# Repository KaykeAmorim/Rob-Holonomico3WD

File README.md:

# Robô Holonômico 3WD

Robô desenvolvido no Colégio Técnico da UFMG (Coltec) com o intuito de auxiliar o ensino de Robótica aos estudantes.

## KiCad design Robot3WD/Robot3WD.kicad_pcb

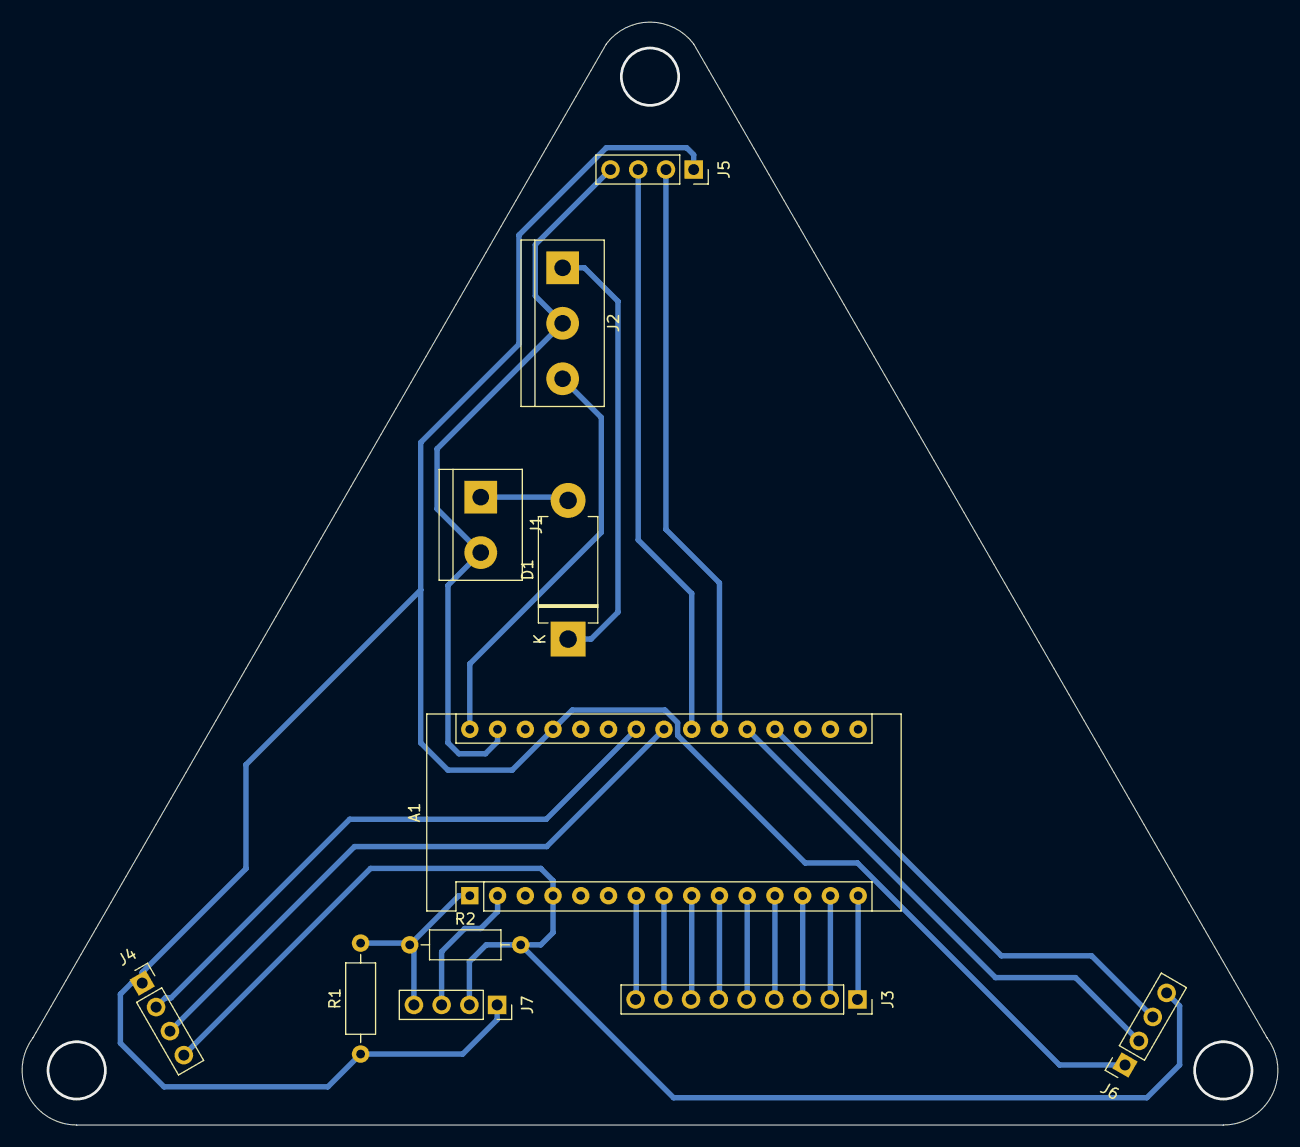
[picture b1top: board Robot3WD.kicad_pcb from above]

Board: 2 copper layers, 115.0 x 101.0 mm, 11 parts (0 on the bottom side), 22 nets.

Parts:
A1: Arduino_Nano_v2.x; Arduino_Nano
D1: 1N5404; D_DO-201AD_P12.70mm_Horizontal
J1: Battery; TerminalBlock_bornier-2_P5.08mm
J2: L298N; TerminalBlock_bornier-3_P5.08mm
J3: Motores; PinSocket_1x09_P2.54mm_Vertical
J4: HC-SR04a; PinSocket_1x04_P2.54mm_Vertical
J5: HC-SR04b; PinSocket_1x04_P2.54mm_Vertical
J6: HC-SR04c; PinSocket_1x04_P2.54mm_Vertical
J7: HC-06; PinSocket_1x04_P2.54mm_Vertical
R1: 1k; R_Axial_DIN0207_L6.3mm_D2.5mm_P10.16mm_Horizontal
R2: 2.2k; R_Axial_DIN0207_L6.3mm_D2.5mm_P10.16mm_Horizontal

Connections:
5v: A1.27, J4.1, J5.1, J6.1, J7.1, R1.1
ENA: A1.15, J3.1
ENB: A1.10, J3.6
ENC: A1.9, J3.7
Echo1: A1.23, J4.3
Echo2: A1.22, J5.3
Echo3: A1.19, J6.3
GND: A1.4, A1.29, J1.2, J2.2, J4.4, J5.4, J6.4, J7.2, R2.2
IN1: A1.14, J3.2
IN2: A1.13, J3.3
IN3: A1.12, J3.4
IN4: A1.11, J3.5
IN5: A1.8, J3.8
IN6: A1.7, J3.9
unnamed: D1.2, J1.1
SRx: A1.1, J7.4, R1.2, R2.1
STx: A1.2, J7.3
Trig1: A1.24, J4.2
Trig2: A1.21, J5.2
Trig3: A1.20, J6.2
Vbat: D1.1, J2.1
Vin: A1.30, J2.3

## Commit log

2022-08-11 Add files via upload
    Impressões 3D
2022-08-11 Add files via upload
    Placa de Circuito Impresso
2022-08-11 Adicionando código, e corrigindo pastas
2022-08-14 Correção da pasta
2022-08-14 Adição de Imagens
2022-08-14 Atualização README
2022-08-14 Nome Imagem
2022-08-22 Correção read me
2022-08-22 Citação
2022-08-23 Adição README
2022-08-23 Correção README
